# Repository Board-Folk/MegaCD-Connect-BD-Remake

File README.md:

# MegaCD-Connect-BD-Remake
This is the Schematics, PCB and Logic for the Mega-CD Connect BD Targeting the 315-5477 (MCE V1) MegaCD.

It is to replace the 837-8327-01 IC BD MEGA-CD CONNECT BD with a failed ASIC to the older Logic version of the board that has the Peel IC.

The board is not a clone, rather a remake as i do not have access to an original logic board version to do an exact replica of traces.

* The Gerbers have been created using the recommendations from JLCPCB.

* This board uses a GAL22V10 to achieve the same logic functions as the Peel IC. Jed file is provided.
  Use a MiniPro to write the Jed file to the GAL Chip.

Notes:- 

 * I have used an ATF22V10B-15PC as a replacement for the GAL22V10. The ATF Works, but i also see this is obsolete. There is ATF22V10C range of chips, but stock seems to be low on these.

 * TESTED V2.0 and this worked, but now made V2.2 and is UNTESTED
   
 * Finally got some GAL20v8 Chips, and they do not work. Think this is a timing issue. So please use the GAL22v10's instead, unless someone wants to take a stab at getting the GAL20v8's to work. (Looks at Steve)

Version 2.3 Changes:-

Updates to Kicad v9, Changed A26/B26 on the CD Expansion to point to 9v, and not 5v. Made no difference with the older version, but made it now match the original PCB.

Added new Logic version, because GALasm was updated and was giving a different compiled version that does not work. Found what i needed to change to make it work.

You can use either Pre-Compiled Jed Files, for the GAL22v10 / ATF22V10

Version 2.2 Changes:-

* Moved traces around the middle screw holes, just incase screw heads sub against the silkscreen removing it and causing a short against the 5v rail.

* Moved the IC1 Silk name slightly up.

Version 2.1 Changes:-

* Moved /TRDIR from PIN 23 to PIN 15, This should make it compatible with the GAL20V8

* Added GAL20V8 Logic, but does not work.

* Updated Labels for Tree House Connection, TH1 and TH2

### Compiling The Logic
---

The software i used to make the Jed file was GALasm. It can be downloaded from here https://github.com/daveho/GALasm

Only source files is provide, so you will need to compile GALasm first. I used MacOS to do this, Linux should work and maybe Windows ???

Once GALasm is compiled, use the following command to compile the Logic into a Jed file from within the GAL22V10 folder.

```
galasm ./GAL22V10.pld
```

### Fitting the Board
---

**1. Post**

---

There is a slight modification required to make the PCB fit in the original housing.

<br>This Post would need a little snip to allow the GAL chip pins to sit correctly in the housing.

**2. Tree House J3**

---

If you use a Pin Header, you will need to bend it slighly inwards otherwise it will not fit inside the MegaCD.

### BOM

---

| Reference | Value                       | Quantity | DigiKey            | Mouser               |
|-----------|-----------------------------|----------|--------------------|----------------------|
| C1 - C6   | 100nf                       | 6        | CL31B104KBCNNNC    | 187-CL31B104KBCNNNC  |
| IC1       | GAL22V10B-15 / ATF22V10B-15 | 1        |                    | 556-AF22V10C15PU     |
| IC2, IC3  | 74HC374                     | 2        | 296-1592-5-ND      | 595-SN74HC374N       |
| IC4       | 74ACT10                     | 1        | CD74ACT10E-ND      | 595-CD74ACT10E       |
| IC5, IC6  | 74HC245                     | 2        | 296-1584-5-ND      | 595-SN74HC245N       |
| RN1, RN2  | 9X-1-472LF (4.7K)           | 2        | 4609X-101-472LF-ND | 652-4609X-1LF-4.7K   |
| J1, J2    | CONN EDGE DF 60POS          | 2        | A112392-ND         | 571-1-5530841-8      |
| J3        | 2 Pin Header 2.54mm         | 1        | 609-4434-ND        | 649-77311-118-02LF   |

[**Interactive BOM**][IBOM]

## Thanks

With thanks to @fabiodl for decoding the logic of the Peel IC

* https://github.com/fabiodl/peelDecoder

#### Other Resources

* https://circuit-board.de/forum/index.php/Thread/25582-SEGA-MEGA-CD-1-Reparatur-PEEL-18CV8-PLD-auslesen/

* https://www.eevblog.com/forum/projects/help-with-reverse-engineering-unexpected-behavior-of-peel18cv8-223204/

### !!!!! WARNING !!!!!

Use at your own risk. I accept no responsibility.

[IBOM]: http://htmlpreview.github.io/?https://raw.githubusercontent.com/chris-jh/MegaCD-Connect-BD-Remake/main/bom/ibom.html

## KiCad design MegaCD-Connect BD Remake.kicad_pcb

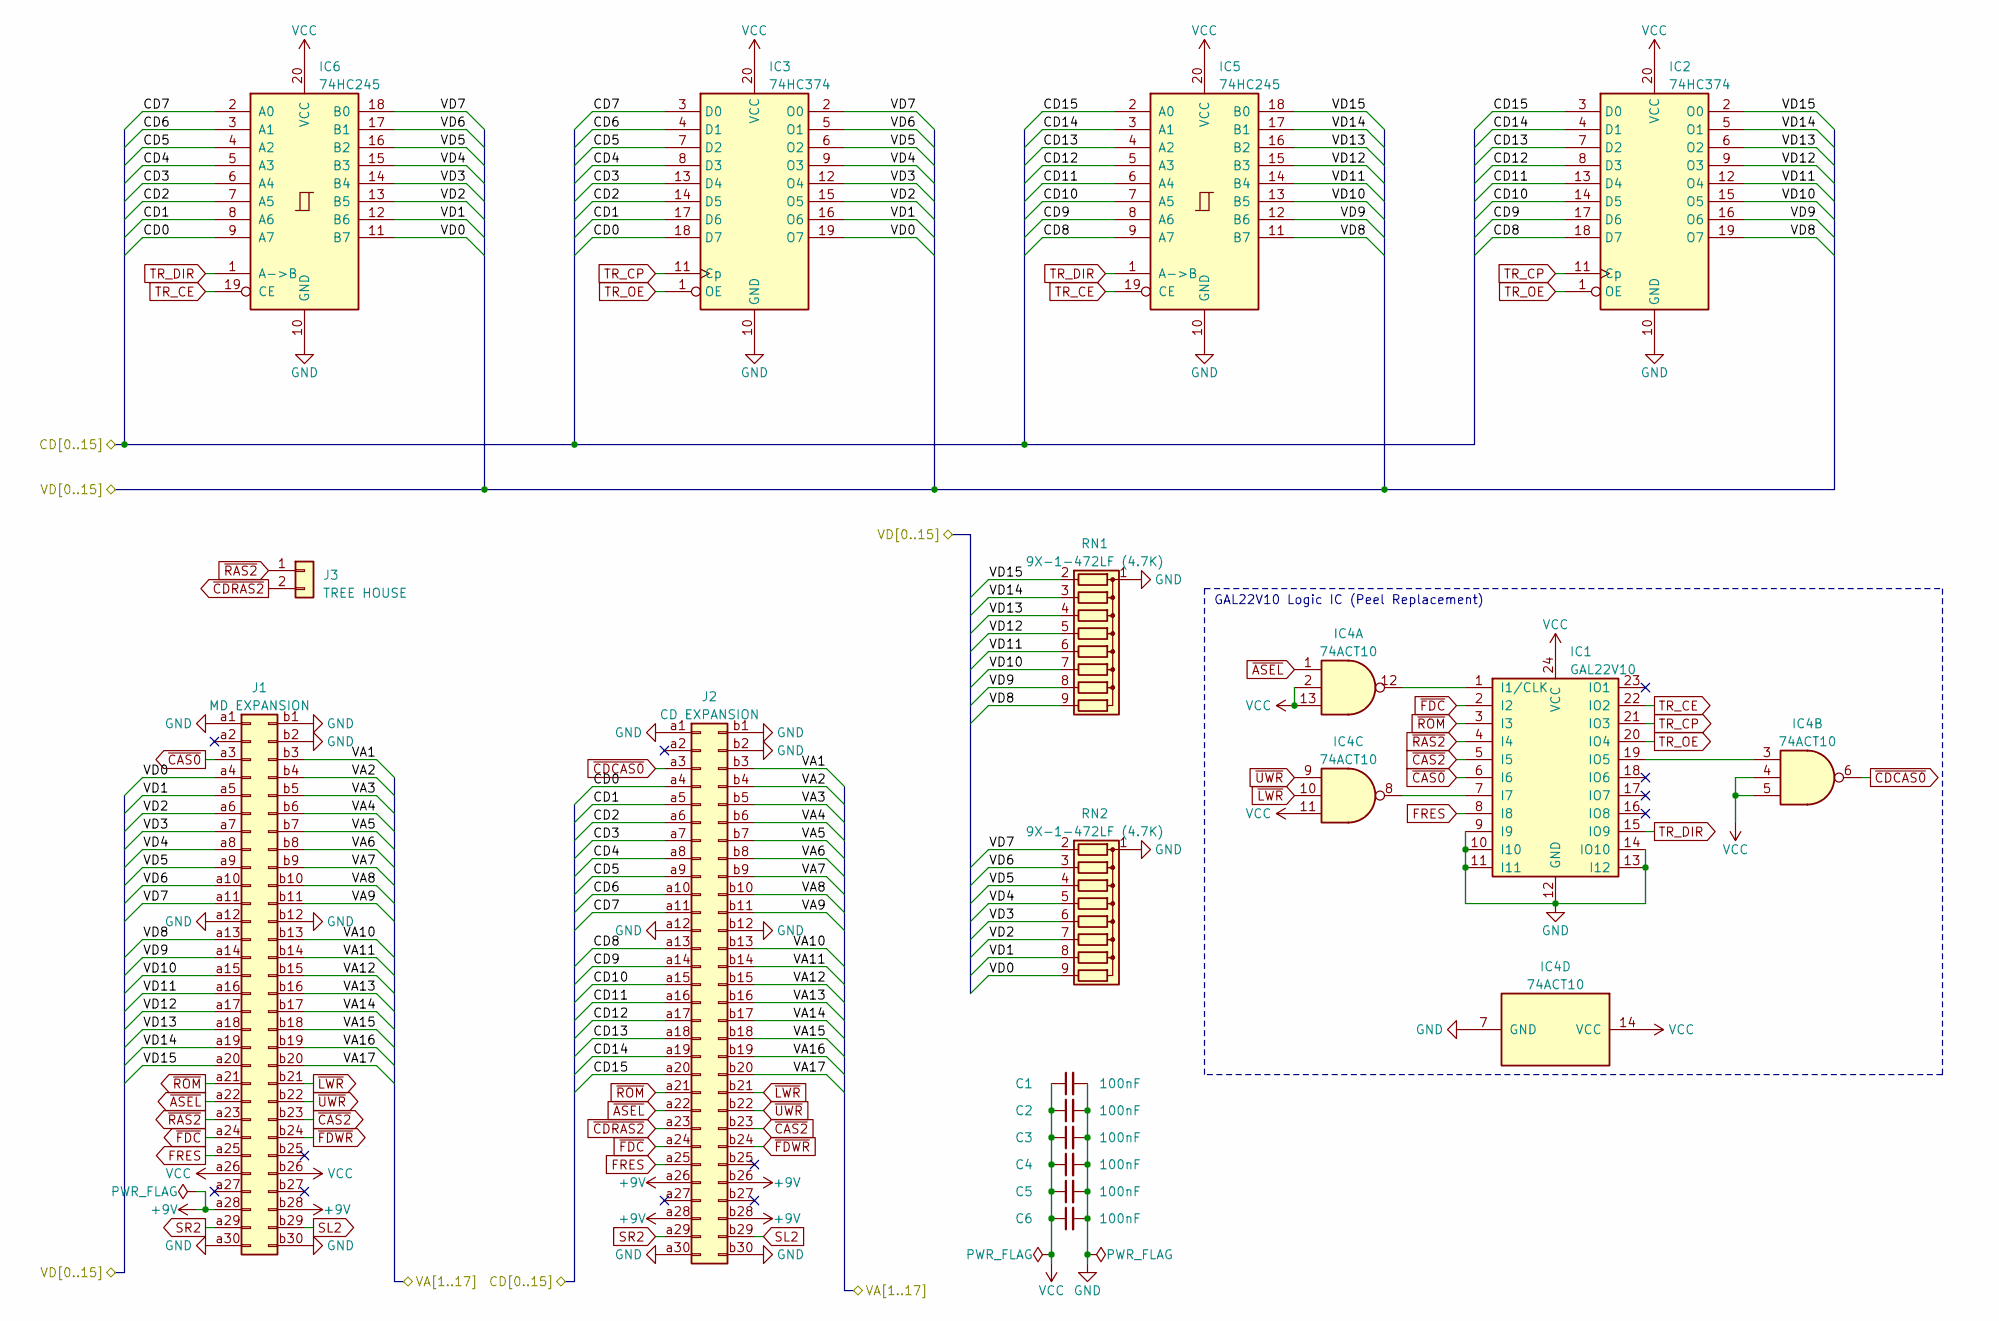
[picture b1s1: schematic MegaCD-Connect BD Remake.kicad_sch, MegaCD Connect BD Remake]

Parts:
C1, C2, C3, C4, C5, C6: 100nF; C_1206_3216Metric
IC1: GAL22V10; DIP-24_W7.62mm_Socket_LongPads
IC2, IC3: 74HC374; DIP-20_W7.62mm_Socket_LongPads
IC4: 74ACT10; DIP-14_W7.62mm_Socket_LongPads
IC5, IC6: 74HC245; DIP-20_W7.62mm_Socket_LongPads
J1: MD EXPANSION; PCB-Connector
J2: CD EXPANSION; PCB-Connector
J3: TREE HOUSE; PinHeader_1x02_P2.54mm_Vertical
RN1, RN2: 9X-1-472LF (4.7K); R_Array_SIP9

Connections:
+9V: J1.a28, J1.b28, J2.a26, J2.a28, J2.b26, J2.b28
/CD0: IC3.18 (D7), IC6.9 (A7), J2.a4
/CD1: IC3.17 (D6), IC6.8 (A6), J2.a5
/CD2: IC3.14 (D5), IC6.7 (A5), J2.a6
/CD3: IC3.13 (D4), IC6.6 (A4), J2.a7
/CD4: IC3.8 (D3), IC6.5 (A3), J2.a8
/CD5: IC3.7 (D2), IC6.4 (A2), J2.a9
/CD6: IC3.4 (D1), IC6.3 (A1), J2.a10
/CD7: IC3.3 (D0), IC6.2 (A0), J2.a11
/CD8: IC2.18 (D7), IC5.9 (A7), J2.a13
/CD9: IC2.17 (D6), IC5.8 (A6), J2.a14
/CD10: IC2.14 (D5), IC5.7 (A5), J2.a15
/CD11: IC2.13 (D4), IC5.6 (A4), J2.a16
/CD12: IC2.8 (D3), IC5.5 (A3), J2.a17
/CD13: IC2.7 (D2), IC5.4 (A2), J2.a18
/CD14: IC2.4 (D1), IC5.3 (A1), J2.a19
/CD15: IC2.3 (D0), IC5.2 (A0), J2.a20
/VA1: J1.b3, J2.b3
/VA2: J1.b4, J2.b4
/VA3: J1.b5, J2.b5
/VA4: J1.b6, J2.b6
/VA5: J1.b7, J2.b7
/VA6: J1.b8, J2.b8
/VA7: J1.b9, J2.b9
/VA8: J1.b10, J2.b10
/VA9: J1.b11, J2.b11
/VA10: J1.b13, J2.b13
/VA11: J1.b14, J2.b14
/VA12: J1.b15, J2.b15
/VA13: J1.b16, J2.b16
/VA14: J1.b17, J2.b17
/VA15: J1.b18, J2.b18
/VA16: J1.b19, J2.b19
/VA17: J1.b20, J2.b20
/VD0: IC3.19 (O7), IC6.11 (B7), J1.a4, RN2.9 (R8)
/VD1: IC3.16 (O6), IC6.12 (B6), J1.a5, RN2.8 (R7)
/VD2: IC3.15 (O5), IC6.13 (B5), J1.a6, RN2.7 (R6)
/VD3: IC3.12 (O4), IC6.14 (B4), J1.a7, RN2.6 (R5)
/VD4: IC3.9 (O3), IC6.15 (B3), J1.a8, RN2.5 (R4)
/VD5: IC3.6 (O2), IC6.16 (B2), J1.a9, RN2.4 (R3)
/VD6: IC3.5 (O1), IC6.17 (B1), J1.a10, RN2.3 (R2)
/VD7: IC3.2 (O0), IC6.18 (B0), J1.a11, RN2.2 (R1)
/VD8: IC2.19 (O7), IC5.11 (B7), J1.a13, RN1.9 (R8)
/VD9: IC2.16 (O6), IC5.12 (B6), J1.a14, RN1.8 (R7)
/VD10: IC2.15 (O5), IC5.13 (B5), J1.a15, RN1.7 (R6)
/VD11: IC2.12 (O4), IC5.14 (B4), J1.a16, RN1.6 (R5)
/VD12: IC2.9 (O3), IC5.15 (B3), J1.a17, RN1.5 (R4)
/VD13: IC2.6 (O2), IC5.16 (B2), J1.a18, RN1.4 (R3)
/VD14: IC2.5 (O1), IC5.17 (B1), J1.a19, RN1.3 (R2)
/VD15: IC2.2 (O0), IC5.18 (B0), J1.a20, RN1.2 (R1)
FRES: IC1.8 (I8), J1.a25, J2.a25
GND: C1.2, C2.2, C3.2, C4.2, C5.2, C6.2, IC1.9 (I9), IC1.10 (I10), IC1.11 (I11), IC1.12 (GND), IC1.13 (I12), IC1.14 (IO10), IC2.10 (GND), IC3.10 (GND), IC4.7 (GND), IC5.10 (GND), IC6.10 (GND), J1.a1, J1.a12, J1.a30, J1.b1, J1.b2, J1.b12, J1.b30, J2.a1, J2.a12, J2.a30, J2.b1, J2.b2, J2.b12, J2.b30, RN1.1 (common), RN2.1 (common)
unnamed: IC1.1 (I1/CLK), IC4.12
unnamed: IC1.7 (I7), IC4.8
unnamed: IC1.19 (IO5), IC4.3
SL2: J1.b29, J2.b29
SR2: J1.a29, J2.a29
TR_CE: IC1.22 (IO2), IC5.19 (CE), IC6.19 (CE)
TR_CP: IC1.21 (IO3), IC2.11 (Cp), IC3.11 (Cp)
TR_DIR: IC1.15 (IO9), IC5.1 (A->B), IC6.1 (A->B)
TR_OE: IC1.20 (IO4), IC2.1 (OE), IC3.1 (OE)
VCC: C1.1, C2.1, C3.1, C4.1, C5.1, C6.1, IC1.24 (VCC), IC2.20 (VCC), IC3.20 (VCC), IC4.2, IC4.4, IC4.5, IC4.11, IC4.13, IC4.14 (VCC), IC5.20 (VCC), IC6.20 (VCC), J1.a26, J1.b26
~ASEL: IC4.1, J1.a22, J2.a22
~CAS0: IC1.6 (I6), J1.a3
~CAS2: IC1.5 (I5), J1.b23, J2.b23
~CDCAS0: IC4.6, J2.a3
~CDRAS2: J2.a23, J3.2
~FDC: IC1.2 (I2), J1.a24, J2.a24
~FDWR: J1.b24, J2.b24
~LWR: IC4.10, J1.b21, J2.b21
~RAS2: IC1.4 (I4), J1.a23, J3.1
~ROM: IC1.3 (I3), J1.a21, J2.a21
~UWR: IC4.9, J1.b22, J2.b22

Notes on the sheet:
GAL22V10 Logic IC (Peel Replacement)

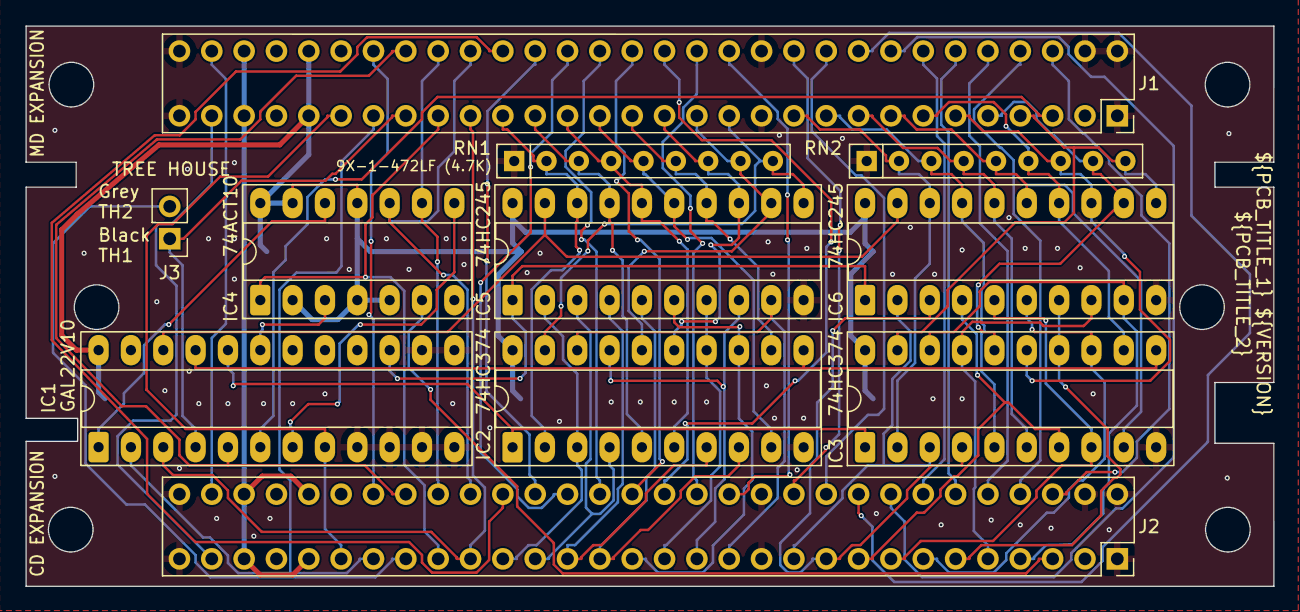
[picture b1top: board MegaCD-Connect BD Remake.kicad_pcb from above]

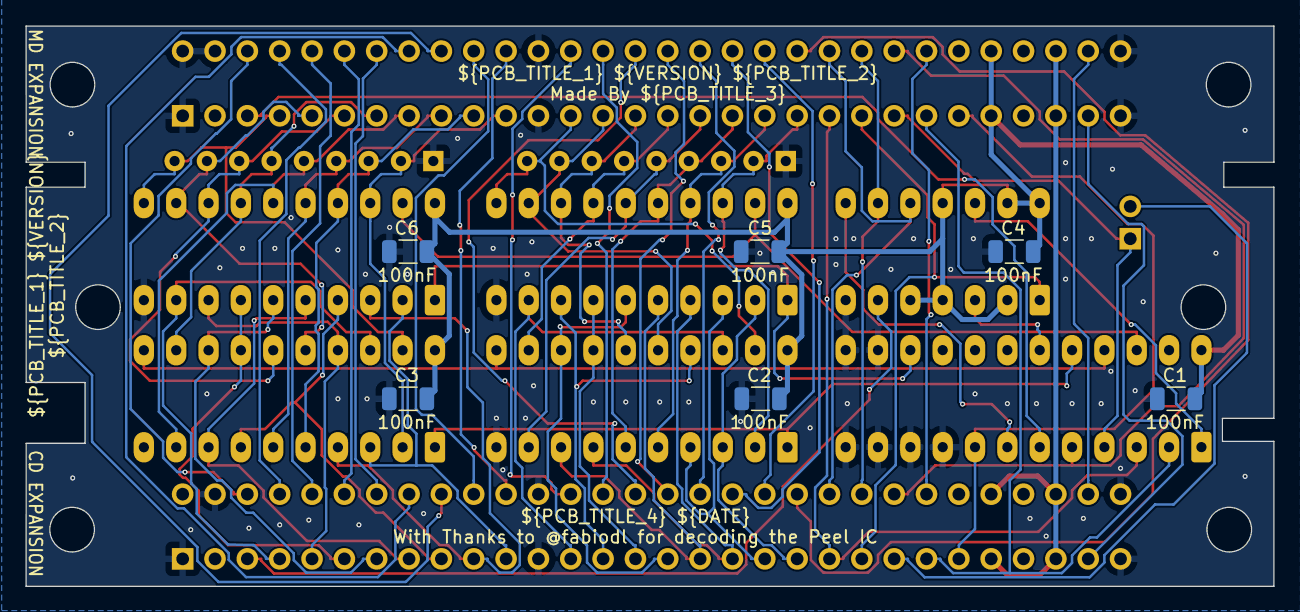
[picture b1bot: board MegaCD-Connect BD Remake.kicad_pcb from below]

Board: 2 copper layers, 98.0 x 44.0 mm, 17 parts (6 on the bottom side), 73 nets.

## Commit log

2023-05-14 Initial Commit
    Initial Commit
2023-05-25 Add code for GAL20V8, move /TRDIR to pin 15 for GAL22V10 as well.
2023-06-03 Update PCB to Version 2.1 * Moved /TRDIR from pin 23 to pin 15 * Added GAL20V8 Logic * Updated Labels for Tree House Connection, TH1 and TH2 * Added an iBom * Updated the ReadMe
2023-06-13 Updated to v2.2
    Moved traces near the two middle screws.
2023-09-29 Update README.md
    Update BOM
2026-01-02 Added fix for when compiling using latest GALasm Jan 2026
2026-01-02 Updated PCB to v2.3 removed A26 B26 Linking to VCC and back to 9V instead on the CD Side Only.
